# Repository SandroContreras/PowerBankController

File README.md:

# Power Bank Controller
Custom 8-cell lithium-ion power bank with embedded monitoring via MicroPython and OLED display.
<br><br>
**Project Status: PCB revision 1 ordered; assembly and electrical validation pending.**
<br><br>
## Overview
This project is a custom 8-cell (8×18650) lithium-ion power bank controller designed to explore
high-current PCB design, USB-C power delivery behavior, and real-world manufacturing constraints.
The board was designed in KiCad and fabricated as a 2-oz copper PCB.

<br>

## Features
- 8× LG MJ1 cells in parallel (~100.8 Wh)
- USB-C power output via IP5310 power-bank SoC
- 2 oz copper PCB for high-current paths
- Per-cell polyfuse protection
- Raspberry Pi Pico for battery monitoring
- Designed for serviceable, replaceable cells

<br>

## How It's Made
**Tech Used:** MicroPython, Raspberry Pi Pico, SSD1306 OLED Display
<br>
Eight 18650 batteries are wired in parallel to a boost converter charging module. The charging module powers the Pico Board and the OLED Display. To achieve battery health displays a voltage divider is used to safely bring down the voltage towards an ADC pin. The display is programmed to display the reported battery health percentage for the user. 

<br><br>

## Design Decisions & Tradeoffs
- Used 18650 holders instead of spot-welded packs to improve safety and serviceability.
- Selected 2 oz copper to reduce voltage drop and thermal stress in high-current paths.
- Chose IP5310 to simplify power-bank control while accepting uncertainty around USB-PD behavior.
- Accepted larger PCB size to prioritize current handling and mechanical robustness.

<br><br>

## Future Work
- Assemble and electrically validate the V1 prototype.
- Verify USB-C charging, 5 V boost output, OLED operation, and Raspberry Pi Pico functionality.
- Perform electrical and thermal testing under sustained load.
- Measure boost converter efficiency and battery runtime with the final 8-cell LG MJ1 battery pack.
- Design and fabricate a custom enclosure suitable for camping use.
- Evaluate the need for a V2 PCB revision based on functional and thermal test results.

<br><br>

## Data Flow

<p align="center"><em>Data flow from ADC voltage reading to OLED UI output.</em></p>

<br><br><br><br><br><br><br><br>

## Circuit Diagram

<p align = "center"><em>High-Level Circuit Diagram.</em></p>

<p align = "center"><em>PCB Circuit Diagram.</em></p> 

<br><br><br>

## Lessons Learned
This project was my first complete custom PCB, from schematic capture through PCB layout, manufacturing, and assembly. Along the way I learned several practical engineering lessons:
    - The importance of verifying component footprints, pinouts, and manufacturer datasheets before ordering parts.
    - How PCB stack-up, copper pours, via placement, and trace widths affect power distribution and thermal performance.
    - The value of building a complete BOM and selecting components based on both electrical requirements and long-term serviceability.
    - That designing a functional hardware system often requires multiple design reviews and may require more than one PCB revision before reaching a mature design.

<br><br><br>

## Included Modules
- 'bisect.py' - From the Python Standard Library (CPython 3.13)
- Source: https://github.com/python/cpython
- License: Python Software Foundation License (PSF)

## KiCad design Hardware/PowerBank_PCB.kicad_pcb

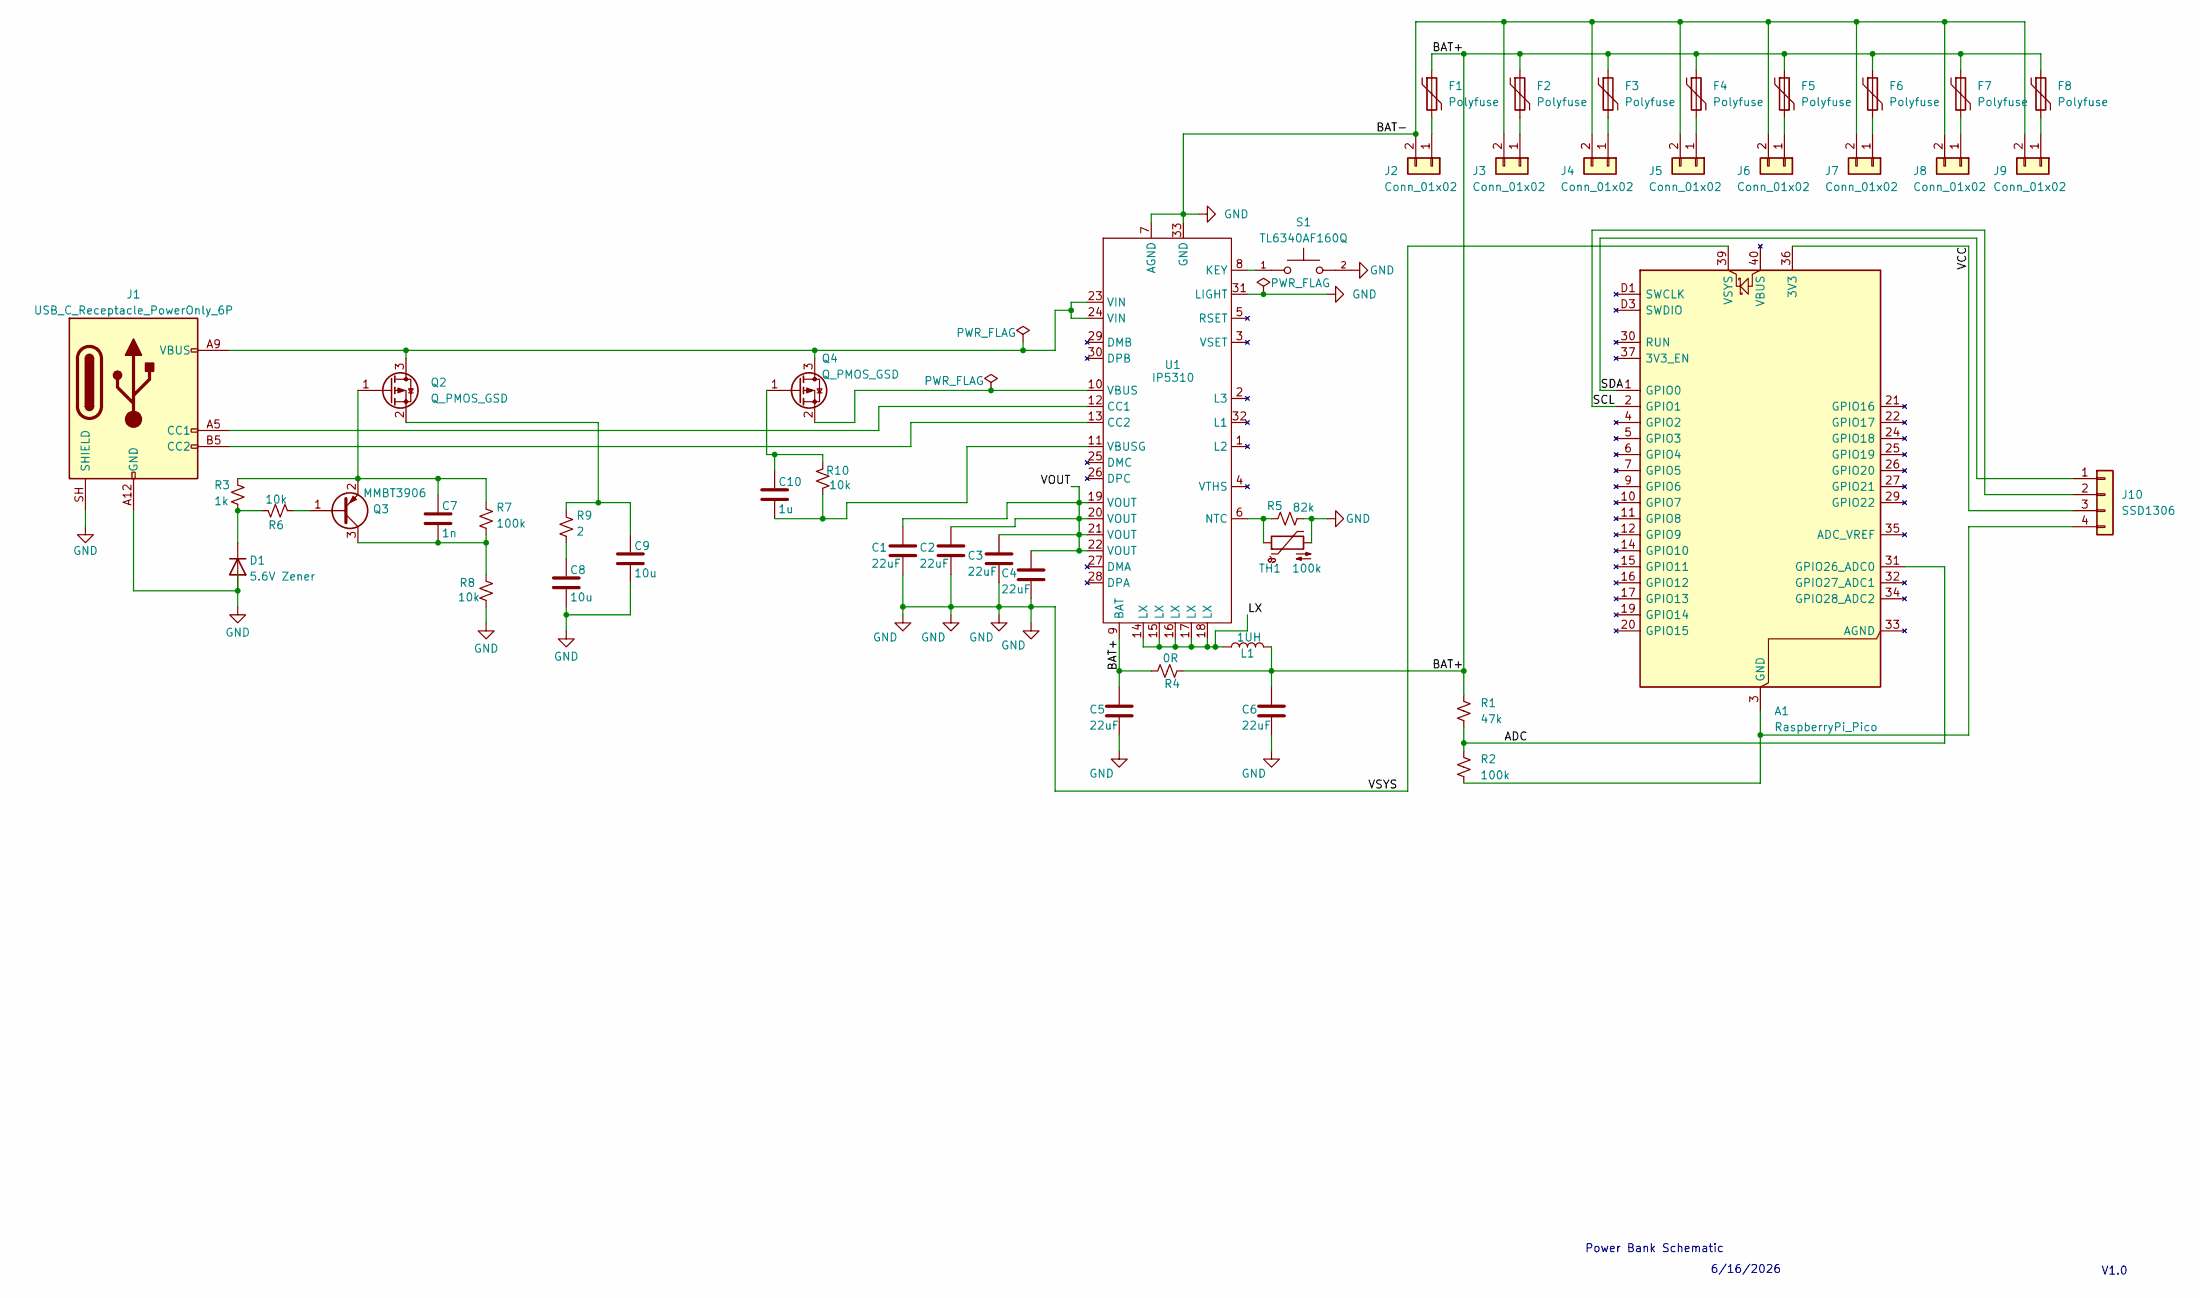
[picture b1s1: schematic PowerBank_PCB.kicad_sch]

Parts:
A1: RaspberryPi_Pico; RaspberryPi_Pico_SMD_HandSolder
C1, C2, C3, C4, C5, C6: 22uF; C_1206_3216Metric_Pad1.33x1.80mm_HandSolder
C7: 1n; C_1206_3216Metric_Pad1.33x1.80mm_HandSolder
C8, C9: 10u; C_1206_3216Metric_Pad1.33x1.80mm_HandSolder
C10: 1u; C_1206_3216Metric_Pad1.33x1.80mm_HandSolder
D1: 5.6V Zener; D_SMA_Handsoldering
F1, F2, F3, F4, F5, F6, F7, F8: Polyfuse; Fuse_1812_4532Metric_Pad1.30x3.40mm_HandSolder
J1: USB_C_Receptacle_PowerOnly_6P; USB_C_Receptacle_GCT_USB4125-xx-x_6P_TopMnt_Horizontal
J2, J3, J4, J5, J6, J7, J8, J9: Conn_01x02; BatteryHolder_Keystone_1042_1x18650
J10: SSD1306; PinHeader_1x04_P2.54mm_Vertical
L1: 1UH; L_6.3x6.3_H3
Q2, Q4: Q_PMOS_GSD; SOT-23_Handsoldering
Q3: MMBT3906; SOT-23_Handsoldering
R1: 47k; R_1206_3216Metric_Pad1.30x1.75mm_HandSolder
R2, R7: 100k; R_1206_3216Metric_Pad1.30x1.75mm_HandSolder
R3: 1k; R_1206_3216Metric_Pad1.30x1.75mm_HandSolder
R4: 0R; R_1206_3216Metric_Pad1.30x1.75mm_HandSolder
R5: 82k; R_1206_3216Metric_Pad1.30x1.75mm_HandSolder
R6, R8, R10: 10k; R_1206_3216Metric_Pad1.30x1.75mm_HandSolder
R9: 2; R_1206_3216Metric_Pad1.30x1.75mm_HandSolder
S1: TL6340AF160Q; SW_TL6340AF160Q; PARTREV 10.23.2019
TH1: 100k; R_1206_3216Metric_Pad1.30x1.75mm_HandSolder
U1: IP5310; QFN-32-1EP_5x5mm_P0.5mm_EP3.3x3.3mm_ThermalVias

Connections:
/ADC: A1.31 (GPIO26_ADC0), R1.2, R2.1
/BAT+: C5.1, C6.1, F1.1, F2.1, F3.1, F4.1, F5.1, F6.1, F7.1, F8.1, L1.2, R1.1, R4.1, R4.2, U1.9 (BAT)
/LX: L1.1, U1.14 (LX), U1.15 (LX), U1.16 (LX), U1.17 (LX), U1.18 (LX)
/SCL: A1.2 (GPIO1), J10.2 (SCL)
/SDA: A1.1 (GPIO0), J10.1 (SDA)
/VCC: A1.36 (3V3), J10.3 (VCC)
/VOUT: C1.1, C2.1, C3.1, C4.1, U1.19 (VOUT), U1.20 (VOUT), U1.21 (VOUT), U1.22 (VOUT)
GND: A1.39 (VSYS), C1.2, C2.2, C3.2, C4.2, C5.2, C6.2, C8.2, C9.2, D1.2 (A), J1.A12 (GND), J1.B12 (GND), J1.SH (SHIELD), J2.2, J3.2, J4.2, J5.2, J6.2, J7.2, J8.2, J9.2, R5.2, R8.2, S1.2, TH1.2, U1.7 (AGND), U1.31 (LIGHT), U1.33 (GND)
unnamed: C8.1, R9.2
unnamed: D1.1 (K), R3.2, R6.1
unnamed: J1.A5 (CC1), U1.12 (CC1)
unnamed: J1.B5 (CC2), U1.13 (CC2)
unnamed: F1.2, J2.1
unnamed: F2.2, J3.1
unnamed: F3.2, J4.1
unnamed: F4.2, J5.1
unnamed: F5.2, J6.1
unnamed: F6.2, J7.1
unnamed: F7.2, J8.1
unnamed: F8.2, J9.1
unnamed: A1.3 (GND), A1.8 (GND), A1.13 (GND), A1.18 (GND), A1.23 (GND), A1.28 (GND), A1.38 (GND), A1.D2 (GND), J10.4 (GND), R2.2
unnamed: J1.A9 (VBUS), J1.B9 (VBUS), Q2.3 (D), Q4.3 (D), U1.23 (VIN), U1.24 (VIN)
unnamed: C7.1, Q2.1 (G), Q3.2 (E), R3.1, R7.1
unnamed: C9.1, Q2.2 (S), R9.1
unnamed: Q3.1 (B), R6.2
unnamed: C7.2, Q3.3 (C), R7.2, R8.1
unnamed: C10.1, Q4.1 (G), R10.1
unnamed: Q4.2 (S), U1.10 (VBUS)
unnamed: S1.1, U1.8 (KEY)
unnamed: R5.1, TH1.1, U1.6 (NTC)
unnamed: C10.2, R10.2, U1.11 (VBUSG)

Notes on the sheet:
6/16/2026
V1.0
Power Bank Schematic

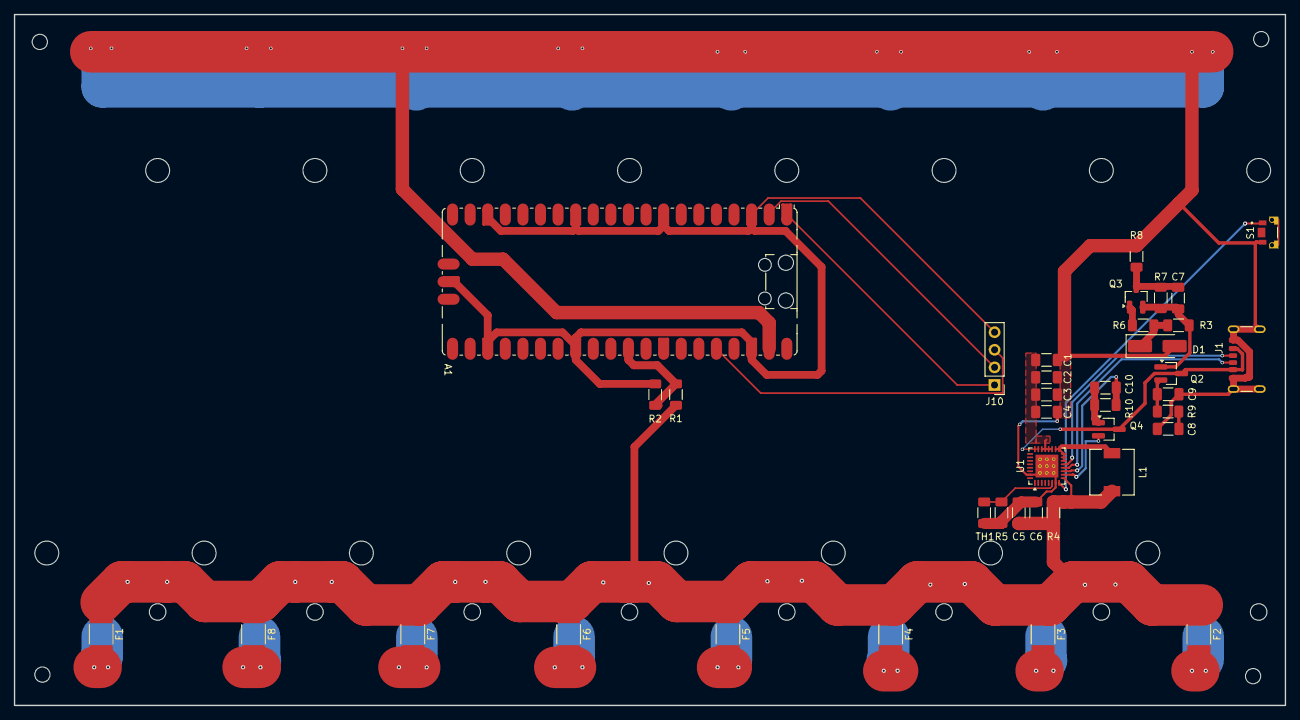
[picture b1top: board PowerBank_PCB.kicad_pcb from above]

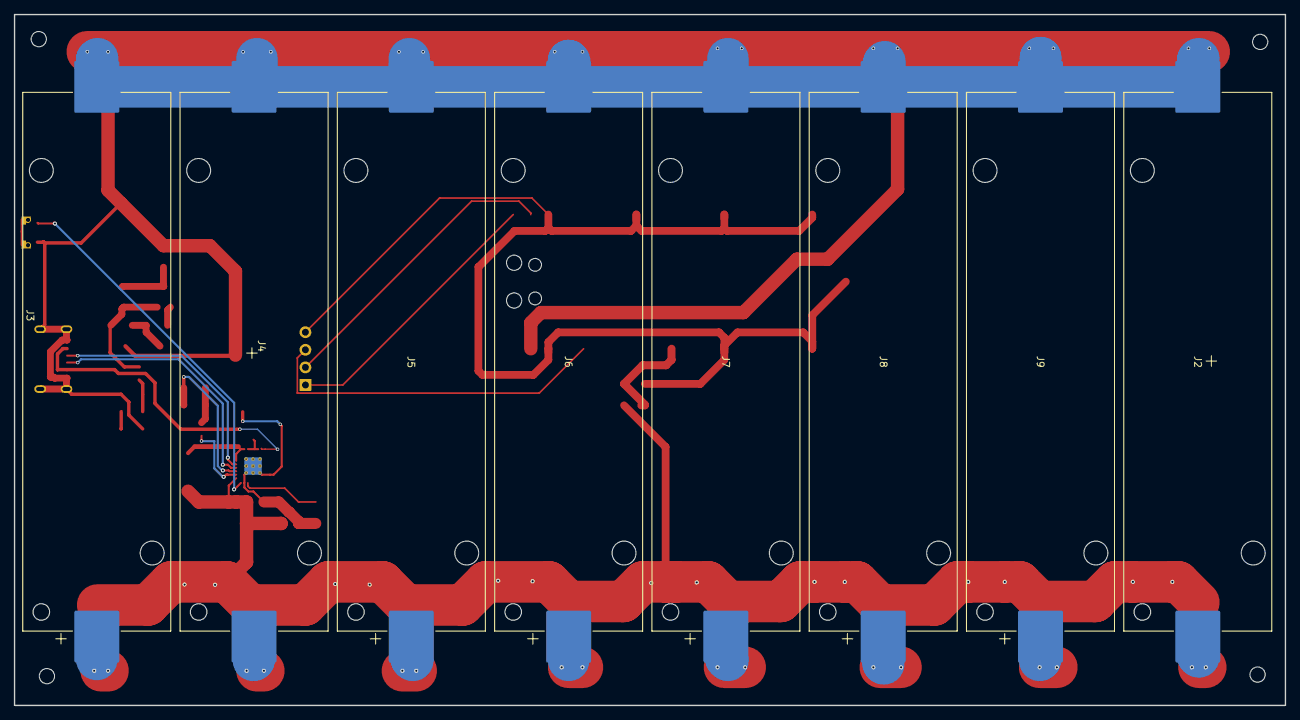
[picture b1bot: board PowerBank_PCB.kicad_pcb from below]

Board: 4 copper layers, 183.5 x 99.8 mm, 47 parts (8 on the bottom side), 31 nets.

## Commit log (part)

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2025-06-13 Delete Comments & Add initials on Code
    I added my initals to the code, and I deleted unused code / comments.
2025-06-15 Updated Battery Status Check
    Due to a lack of Fuel Gauge Chips, now we are using SOC to determine the Battery Health
2025-06-15 Updated Resistor Values
    The resistors used were properly updated in the Battery Voltage math
2025-06-15 Update main.py Resistor value again
2025-06-16 Implemented SMA for Voltages
    Added SMA to reduce noise in Battery Voltage Calculations, for use in the SOC table
2025-06-16 Transformed Code into Functions
    I took loose code and created functions to clean up the While Loop sequence.
2025-06-22 Optimized SMA function and Added Battery Symbol
    Reworked the SMA function, and a Battery Symbol drawing was pushed to the OLED. The "Battery:" text display was removed from the Display. The Battery Symbol will be on the upper left, alongside the b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
2025-06-25 Implemented New Logic Display Rules
    Added new logic for shifting the Percentage % Symbol depending on whether the battery health is single-digit or double-digit. Added Logic to display the Charging Symbol ONLY when the Power Bank is Ch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
2025-06-25 Fixed SMA function
    Fixed the SMA value append bug and moved the return value outside the while loop.
2025-06-25 Fixed Value Loss Bug
    Now we are using variable battery_voltage to capture the result of the Battery Voltage SMA function to capture the latest SMA value.
2025-06-25 Removed Global Variable
    Replaced the Global battery_voltage variable by passing the battery_voltage variable to the BatteryVoltage_SMA() function.
2025-06-28 Refactored Code (Moved into a Function)
    I moved the power reading code into a PowerCalculator() function. I moved the previous_battery_voltage code into the while loop, which uses the new function. I added an if-elif statement structure th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
2025-06-28 Added Battery Symbol Fillings
    I added the necessary drawings needed to fill the battery symbol quadrants when the battery voltage conditionals are met.
2025-06-30 Refactor: converted codebase to OOP design
    All functions were moved into classes, and methods were created. The code will be tested shortly. The code base is now in OOP form.
2025-06-30 Fixed Syntax Errors
    Syntax Errors are now cleared. Next, I will ensure the program functions again with classes now.
2025-06-30 Program Functions
    The Program appears to function within the IDE. There are no more errors. I started the parallel list for the voltage and percentage comparisons.
2025-07-14 Created PowerBank.py Class File
    I created the PowerBank.py Class file which now contains all previous classes from main.py. The program is buggy currently, fixes are coming soon.
2025-07-15 Voltage Readings Function
    Raw voltage data is flowing through the output terminal. Next, debug the array of voltages.
2025-07-16 OLED Display Functions
    Now the OLED is displaying as directed in the OledSignal Method
2025-07-16 Rearranged UI Symbols
    I moved the battery percentage value and symbol next to the battery symbol on the left. The charging symbol will now flash on the right side of the battery health percentage symbol.
2025-07-25 Increased SMA Window & Added new Variables
    I increased the SMA window from 12 to 60 to smooth out the battery voltages. I added new variables, time & updated_time to eventually use the time method to implement a throttler for the OLED display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
2025-07-27 Optimized SOC table utilizing Bisect_left()
    Optimized the SOC table range by using bisect.bisect_left() to reduce time complexity for 14 conditions.
2025-07-30 Implemented SetWindowSize() method
    Created SetWindowSize(battery_voltage) method to adjust SMA Window Size according to 18650's non-linear voltage curve. When the 18650s have less than 3.9 V present, noise is greater, so a larger wind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
2025-07-31 Functions w/o Errors, Incomplete Logic
    Code Functions, but Logic needs to be completed, and the program must be stabilized.
2025-08-02 Modularized OledSignal() method
    I modularized the OledSignal() method by transferring its contents into modular method calls. New methods established: DrawBatteryPercentage(battery_voltage, percentSymbol, battery_percent_str), Draw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
2025-08-02 Update LICENSE
2025-08-02 Updated main.py comments to improve Professionalism
    Just trying to polish things up.
2025-08-02 Update PowerBank.py
    Credited the library SSD1306
2025-08-04 Implemented Boot Up Message
    New method BootMSG() defined to push bootup message. Window Size check implemented, incomplete.
2025-08-08 Organize project files: New directories
    Added code/ and images/ directories for python scripts and data flow charts to be stored.
2025-08-08 Added Data Flowchart to README.md
2025-08-08 Removed loose files.
2025-08-10 Fixed Array Sharing Issue / Added WindowSize Check
    Now the BatteryVoltageArr is shared across both classes correctly. A window size checker was implemented to display a boot message until the window size is met. Now I must stabilize the power stagnat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
2025-08-10 Removed unnecessary files for improved organization purposes
2025-08-10 Delete images directory
    Unnecessary Directory in this branch
2025-08-13 Improved SMA method / Debugged Program
    Revamped SMA method with new implementation. Improved code stability by utilizing SMA_battery_voltage instead of the raw battery_voltage input throughout display logic. Now SMA method uses raw voltag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
2025-08-13 Restore images/ directory from previous main version
2025-08-14 Circuit Diagram Added
2025-08-14 Portable Power Bank Diagram Tweaks
2025-08-15 Design Improvements
    Captures SMA in main loop for single truth source. OledSignal() call now utilizes captured SMA value, sharing SMA_battery_voltage instance across classes. Now FillBatteryQuadrant() uses SMA_battery_v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
2025-08-16 Implemented Check_movingAvgArr() Method
    Check_movingAvgArr method ensures that SMA has occured at least once, which will return a True boolean, otherwise it returns a False boolean. This method drives smooth UI startup after SMA bootup is 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
2025-08-16 Update PowerBank.py
    removed unnecessary comment
2025-08-18 Fixed SMA Bug / Improved Boot time
    SMA function was fixed by implemnting the appending of a new value within the second boolean condition of the SMA method. Boot time was improved significantly by reducing sleep time from 5 seconds to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
2025-08-18 Update PowerBank.py
    removed extra Array.pop(0) inside of SMA function
2025-08-18 Code is fairly stable, just need to implment idle logic
    main function is stable aside from unstable idle power bank logic.
2025-12-13 Implemented Moving Average Array Storage Limit
    Limited Moving Average Array to 60 elements to prevent memory crash.
2025-12-23 Removed Idle Logic
    Idle logic is no longer required, as we intend to utilize key pin on charging module.
2025-12-25 Final Polished Version
    Ensured all UI components rely soley on SMA voltages. Deleted
    GetPowerDifference() function, as power differences will be handled by
    charging module.
2025-12-25 Functional UI Program
2025-12-29 Improved Battery Symbol UI & Refactored Boot Logic to SMA Dependency
    Improved Battery Symbol UI through incrementing the rectangle widths as needed. Now the boot logic depends on a boolean tracking if SMA occurred. This switch enables functional use of OLED during mod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
2025-12-30 Corrected Use of self. objects in codebase
    Simplified codebase through correcting improper usage of self. throughout the codebase. Now all elements utilize the objects.
2025-12-30 Scaled down SOC table
    Scaled down SOC table voltage elements beyond 3.95 V. Testing revealed system voltage ceiling to be 4.07V. Scaled down to accurately display battery life percentage.
2026-01-19 Added PCB Schematic
    This is the low-level schematic of our PCB.
2026-01-20 Updating PCB Schematic Image
2026-01-20 Updating High-Level Schematic image
2026-01-20 Added PCB files
2026-06-14 Implemented proper Circuit for USB-C Input/Output
    Implemented PMOS transistors to provide USB-C Input/Output functionalities
2026-06-17 Added Correct Footprints
    The Schematic is now completed with the correct Foot Prints
